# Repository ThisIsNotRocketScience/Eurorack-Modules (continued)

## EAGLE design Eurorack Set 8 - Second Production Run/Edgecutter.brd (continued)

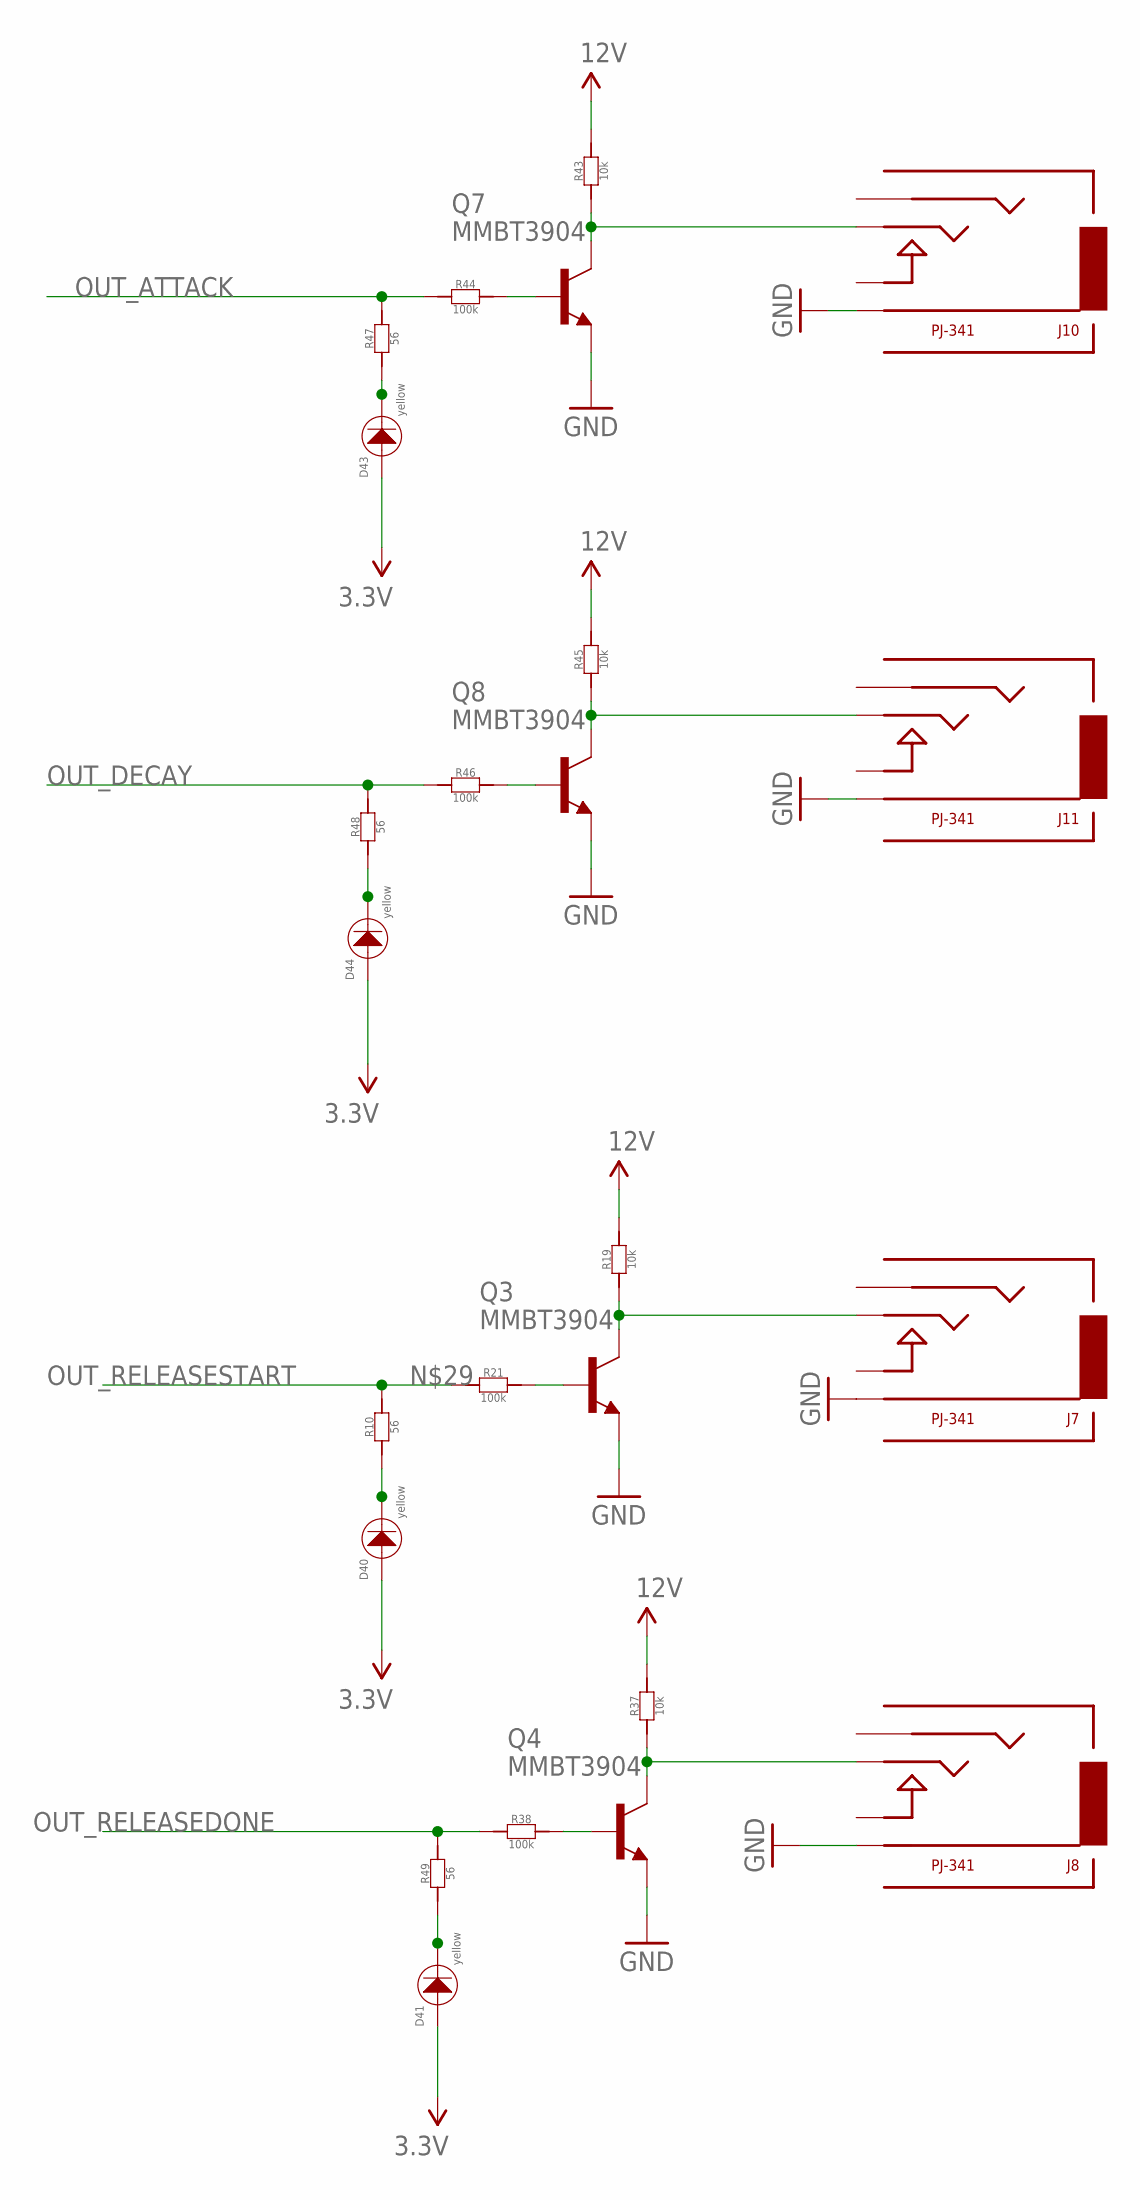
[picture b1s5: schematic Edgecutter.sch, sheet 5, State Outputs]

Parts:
D40, D41, D43, D44: yellow; 3MMLED
J7, J8, J10, J11: PJ-341; 3.5MM-JACK-SWITCH-13MM-OUTPUT
Q3, Q4, Q7, Q8: MMBT3904; SOT23-BEC; MPN PMBT3904,215
R10, R47, R48, R49: 56; R0603
R19, R37, R43, R45: 10k; R0603
R21, R38, R44, R46: 100k; R0603

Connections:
3.3V: D40.+, D41.+, D43.+, D44.+; also elsewhere on the board
12V: R19.2, R37.2, R43.2, R45.2; also elsewhere on the board
D21: D43.-, R47.1
GND: J7.RING@3 (RING), J8.RING@3 (RING), J10.RING@3 (RING), J11.RING@3 (RING), Q3.E, Q4.E, Q7.E, Q8.E; also elsewhere on the board
unnamed: D40.-, R10.1
unnamed: Q3.B, R21.2
unnamed: J7.TIP@3 (TIP), Q3.C, R19.1
unnamed: D41.-, R49.1
unnamed: D44.-, R48.1
unnamed: Q4.B, R38.2
unnamed: J8.TIP@3 (TIP), Q4.C, R37.1
unnamed: Q7.B, R44.2
unnamed: J10.TIP@3 (TIP), Q7.C, R43.1
unnamed: Q8.B, R46.2
unnamed: J11.TIP@3 (TIP), Q8.C, R45.1
OUT_ATTACK: R44.1, R47.2; also elsewhere on the board
OUT_DECAY: R46.1, R48.2; also elsewhere on the board
OUT_RELEASEDONE: R38.1, R49.2; also elsewhere on the board
OUT_RELEASESTART: R10.2, R21.1; also elsewhere on the board

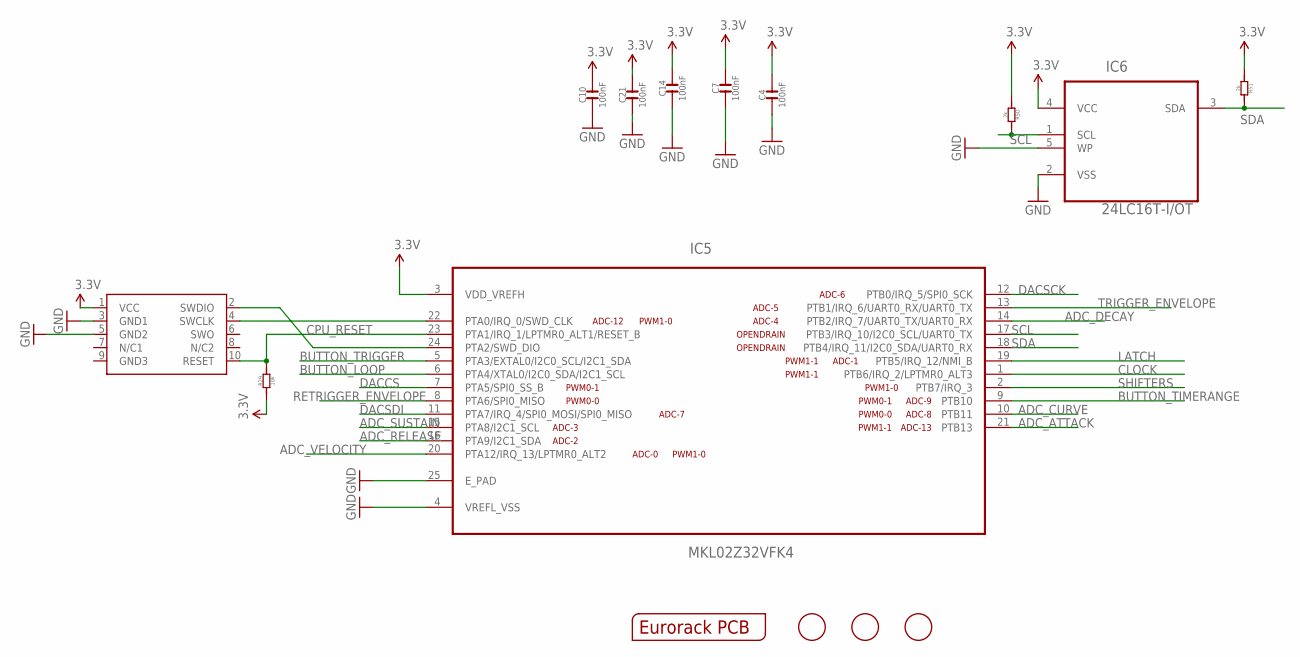
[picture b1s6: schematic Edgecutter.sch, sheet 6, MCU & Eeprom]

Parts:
C4, C7, C10, C14, C21: 100nF; C0603; MPN MC0603F104Z160CT
FID1, FID2, FID3: FIDUCIAL; FIDUCIAL_1MM
IC5: MKL02Z32VFK4; QFN50P400X400X100-25N
IC6: 24LC16T-I/OT; SOT95P290X145-5N; MPN 24LC16T-I/OT
OUTLINE: EURORACK_PCB12HP; EURORACK12HPPCB
R29: 10k; R0603
R50, R51: 2k; R0603
SWD1: CORTEX_SWD; M50-3600542

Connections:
3.3V: C4.2, C7.2, C10.2, C14.2, C21.2, IC5.3 (VDD_VREFH), IC6.4 (VCC), R29.1, R50.1, R51.1, SWD1.1 (VCC); also elsewhere on the board
ADC_ATTACK: IC5.21 (PTB13); also elsewhere on the board
ADC_CURVE: IC5.10 (PTB11); also elsewhere on the board
ADC_DECAY: IC5.14 (PTB2/IRQ_7/UART0_TX/UART0_RX); also elsewhere on the board
ADC_RELEASE: IC5.16 (PTA9/I2C1_SDA); also elsewhere on the board
ADC_SUSTAIN: IC5.15 (PTA8/I2C1_SCL); also elsewhere on the board
ADC_VELOCITY: IC5.20 (PTA12/IRQ_13/LPTMR0_ALT2); also elsewhere on the board
BUTTON_LOOP: IC5.6 (PTA4/XTAL0/I2C0_SDA/I2C1_SCL); also elsewhere on the board
BUTTON_TIMERANGE: IC5.9 (PTB10); also elsewhere on the board
BUTTON_TRIGGER: IC5.5 (PTA3/EXTAL0/I2C0_SCL/I2C1_SDA); also elsewhere on the board
CLOCK: IC5.1 (PTB6/IRQ_2/LPTMR0_ALT3); also elsewhere on the board
CPU_RESET: IC5.23 (PTA1/IRQ_1/LPTMR0_ALT1/RESET_B), R29.2, SWD1.10 (RESET)
DACCS: IC5.7 (PTA5/SPI0_SS_B); also elsewhere on the board
DACSCK: IC5.12 (PTB0/IRQ_5/SPI0_SCK); also elsewhere on the board
DACSDI: IC5.11 (PTA7/IRQ_4/SPI0_MOSI/SPI0_MISO); also elsewhere on the board
GND: C4.1, C7.1, C10.1, C14.1, C21.1, IC5.4 (VREFL_VSS), IC5.25 (E_PAD), IC6.2 (VSS), IC6.5 (WP), SWD1.3 (GND1), SWD1.5 (GND2); also elsewhere on the board
LATCH: IC5.19 (PTB5/IRQ_12/NMI_B); also elsewhere on the board
RETRIGGER_ENVELOPE: IC5.8 (PTA6/SPI0_MISO); also elsewhere on the board
SCL: IC5.17 (PTB3/IRQ_10/I2C0_SCL/UART0_TX), IC6.1 (SCL), R50.2
SDA: IC5.18 (PTB4/IRQ_11/I2C0_SDA/UART0_RX), IC6.3 (SDA), R51.2
SHIFTERS: IC5.2 (PTB7/IRQ_3); also elsewhere on the board
SWD_CLK: IC5.22 (PTA0/IRQ_0/SWD_CLK), SWD1.4 (SWCLK)
SWD_DIO: IC5.24 (PTA2/SWD_DIO), SWD1.2 (SWDIO)
TRIGGER_ENVELOPE: IC5.13 (PTB1/IRQ_6/UART0_RX/UART0_TX); also elsewhere on the board

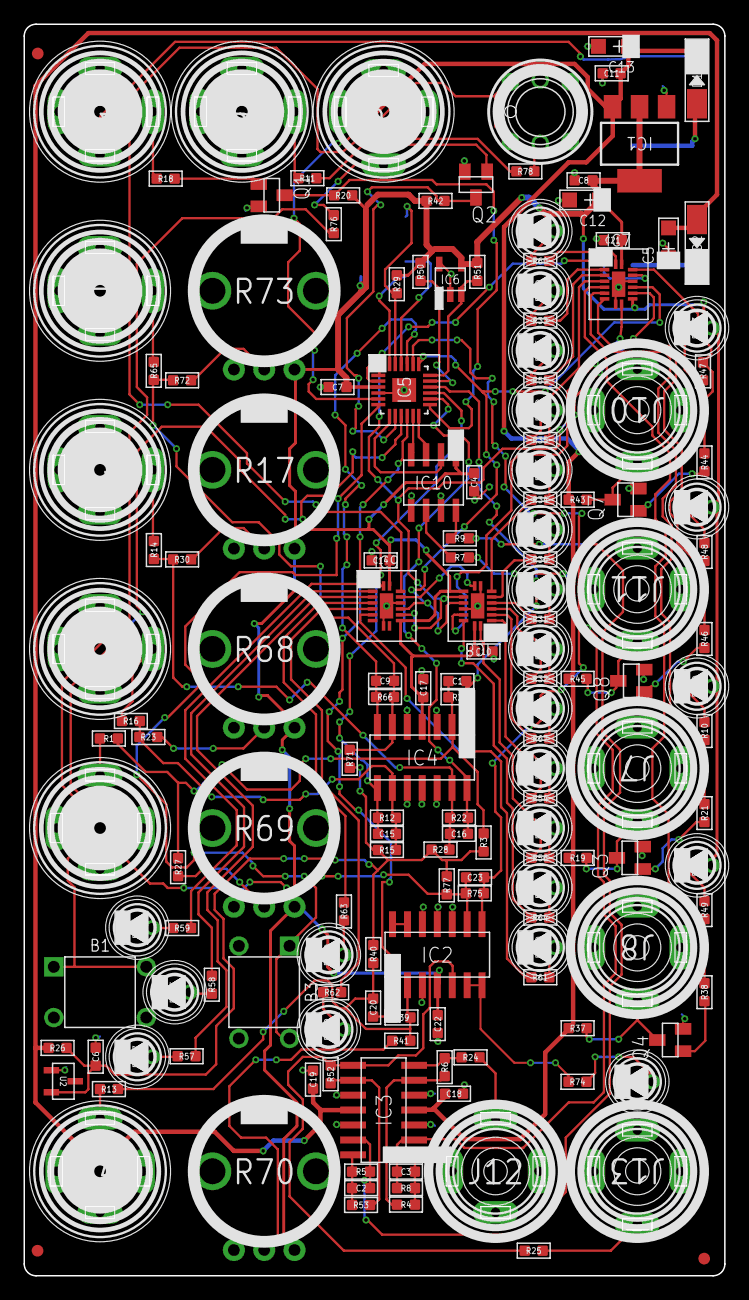
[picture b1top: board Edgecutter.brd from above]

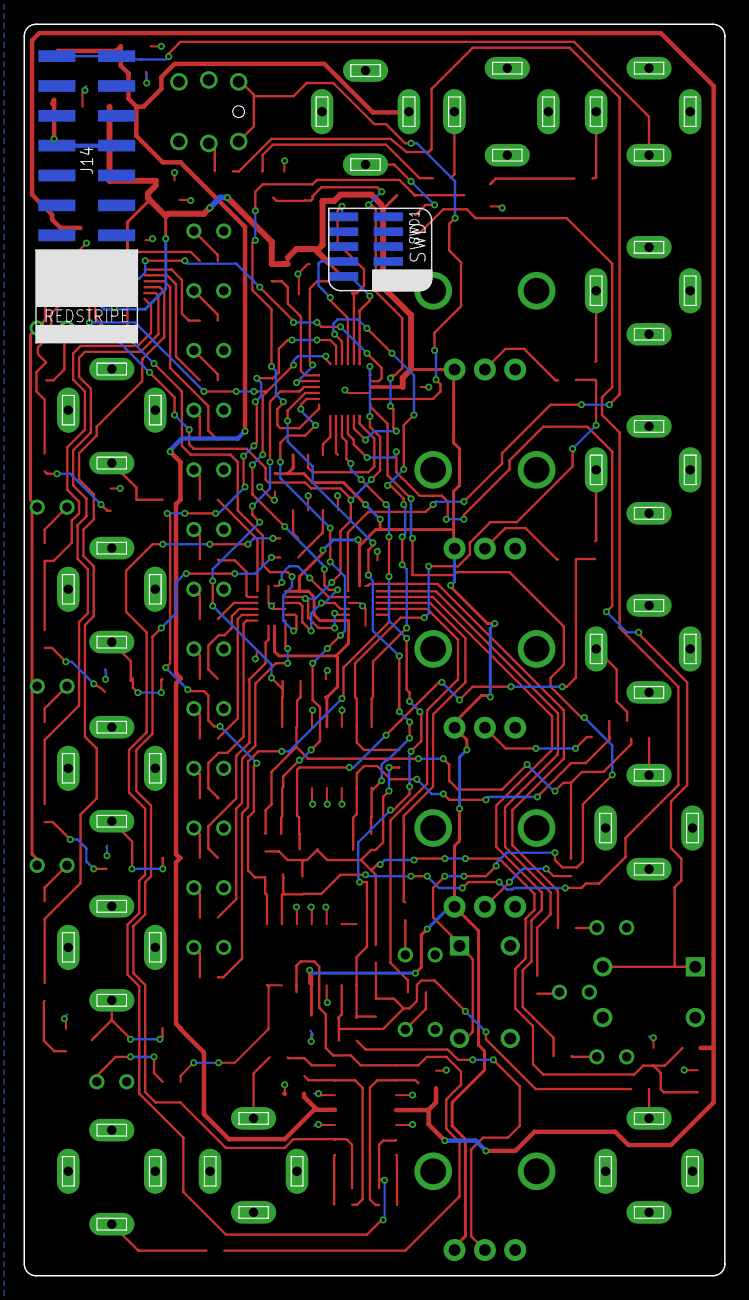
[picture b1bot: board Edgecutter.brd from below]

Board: 2 copper layers, 59.6 x 106.5 mm, 166 parts (2 on the bottom side), 122 nets.

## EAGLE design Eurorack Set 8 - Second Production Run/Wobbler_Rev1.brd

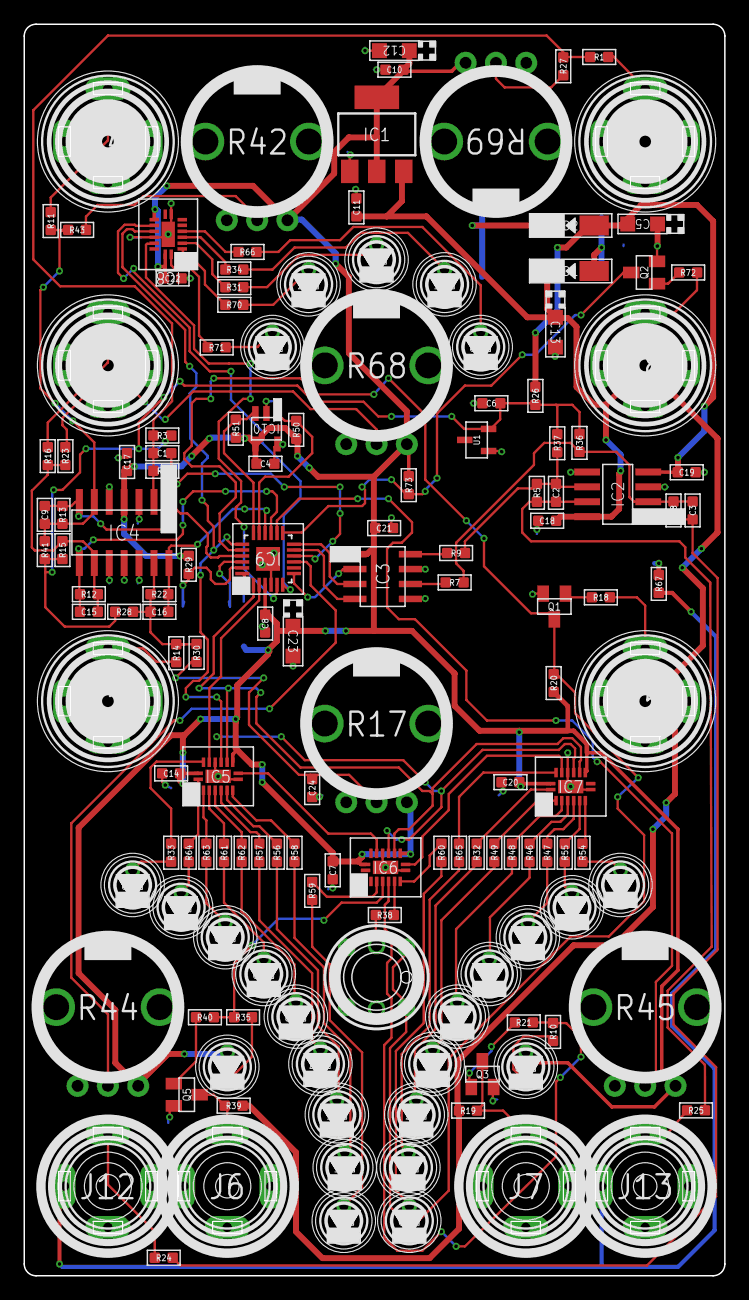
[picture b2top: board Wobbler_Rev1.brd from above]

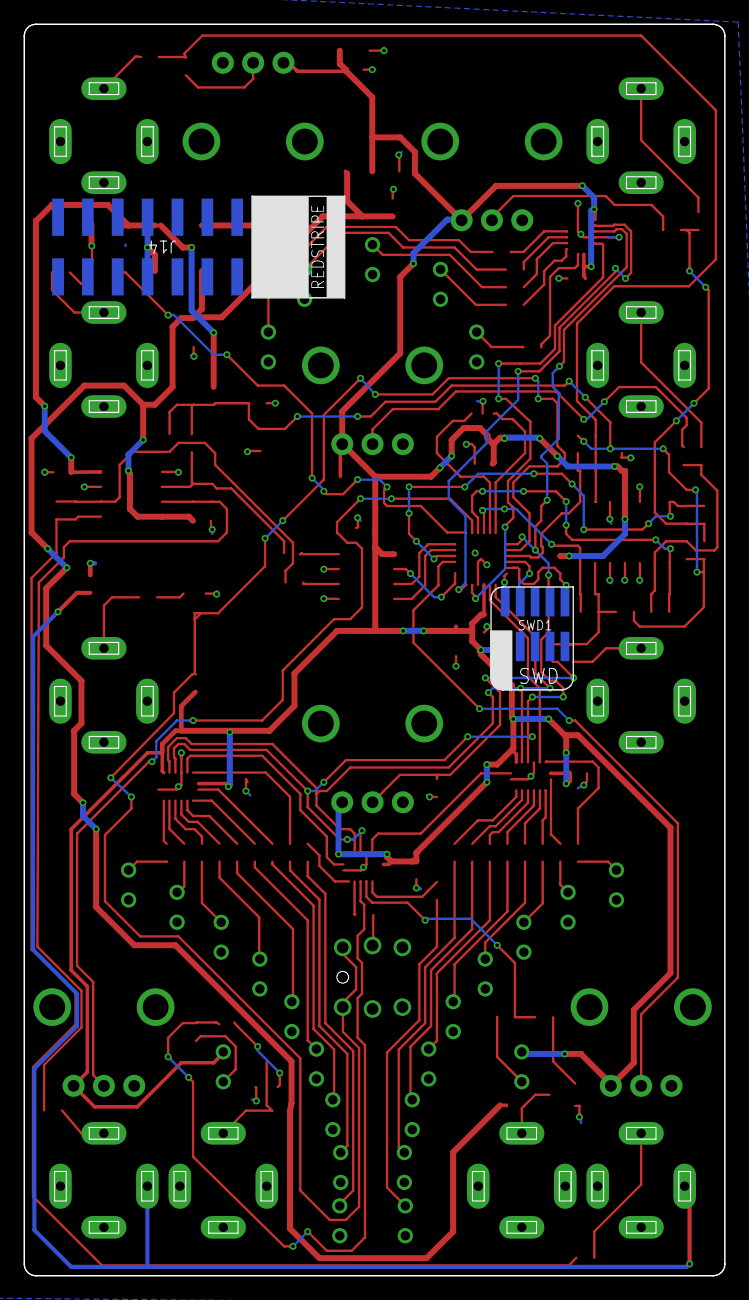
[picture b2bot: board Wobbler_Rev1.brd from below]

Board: 2 copper layers, 59.6 x 106.5 mm, 149 parts (2 on the bottom side), 111 nets.

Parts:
C1, C9, C15, C16: 3.3nF; C0603
C2: 3.3nF C0G; C0603
C3: 3.3nF COG; C0603
C4, C6, C7, C8, C10, C11, C14, C17, C18, C19, C20, C21, C22, C24: 100nF; C0603
C5, C12, C13, C23: 10uF; AVX-A
D1, D2: MRA4004T3G; DO-214AC
D3, D4, D5, D6, D7, D8, D9, D10, D11, D12, D13, D14, D24, D25, D26, D27, D28, D29, D30, D31, D32, D33, D34, D35, D40: yellow; 3MMLED
IC1: LD1117AS33TR; SOT223
IC2: TL072; SO08
IC3: MCP4822-E/SN; SOIC8-N_MC
IC4: MCP6004; SO14
IC5, IC6, IC7, IC8: 74HC595BQ; QFN50P250X350X100-17N
IC9: MKL02Z32VFK4; QFN50P400X400X100-25N
IC10: 24LC16T-I/OT; SOT95P290X145-5N
J1, J2, J3, J4, J5, J8: PJ-341; 3.5MM-JACK-SWITCH-13MM-INPUT
J6, J7, J12, J13: PJ-341; 3.5MM-JACK-SWITCH-13MM-OUTPUT
J14: POWERSMT; 2X08_SMT_HEADER
OUTLINE: EURORACK_PCB12HP; EURORACK12HPPCB
Q1, Q2, Q3, Q5: MMBT3904; SOT23-BEC
R1, R11, R14, R16, R18, R21, R40, R72: 100k; R0603
R2, R12, R13, R22, R23, R27, R30, R43: 33k; R0603
R3, R15, R28, R41: 51k; R0603
R5, R8, R36, R37: 187k 0.1%; R0603
R7, R9: 38.3k 0.1%; R0603
R10, R31, R32, R33, R34, R35, R38, R46, R47, R48, R49, R54, R55, R56, R57, R58, R59, R60, R61, R62, R63, R64, R65, R66, R70, R71: 56; R0603
R17, R42, R44, R45, R68, R69: 10kB; OG-POTS_ALPS_POT_VERTICAL
R19, R20, R26, R29, R39, R73: 10k; R0603
R24, R25: 100; R0603
R50, R51: 2k; R0603
R67: 0; R0603
SWD1: CORTEX_SWD; M50-3600542
U1: LM4040DIM3-5.0; SOT95P237X112-3N
U$1: SWITCH_W_LED_PB6149L-X-102YELLOW; PB6149L

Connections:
3.3V: C4.2, C7.2, C8.2, C10.2, C12.+, C14.2, C17.1, C20.2, C21.2, C22.2, C23.+, D3.+, D40.+, IC1.2, IC1.4, IC3.1, IC4.4, IC5.10, IC5.16, IC6.10, IC6.16, IC7.10, IC7.16, IC8.10, IC8.16, IC9.3, IC10.4, R17.P$3, R20.2, R29.1, R42.P$3, R44.P$3, R45.P$3, R50.1, R51.1, R68.P$3, R69.P$3, R73.2, SWD1.1
12V: C11.2, C13.+, C18.2, D1.2, IC1.3, IC2.8, R19.2, R39.2
-12V: C5.-, C19.2, D2.1, IC2.4, R26.1
ADC_FREQ: C16.2, IC4.14, IC9.16, R22.1
ADC_MOD: C1.2, IC4.1, IC9.21, R2.1
ADC_NORMAL: IC9.9, R44.P$2
ADC_PHASE: C9.2, IC4.7, IC9.10, R13.1
ADC_PHASED: IC9.14, R45.P$2
ADC_SHAPE: C15.2, IC4.8, IC9.15, R12.1
CLOCK: IC5.11, IC6.11, IC7.11, IC9.1
CLOCK_2: IC8.11, IC9.6
CPU_RESET: IC9.23, R29.2, SWD1.10
DACCS: IC3.2, IC9.7
DACSCK: IC3.3, IC9.12
DACSDI: IC3.4, IC9.11
GND: C4.1, C5.+, C6.1, C7.1, C8.1, C10.1, C11.1, C12.-, C13.-, C14.1, C17.2, C18.1, C19.1, C20.1, C21.1, C22.1, C23.-, C24.2, D4.-, D5.-, D6.-, D7.-, D8.-, D9.-, D10.-, D11.-, D12.-, D13.-, D14.-, D24.-, D25.-, D26.-, D27.-, D28.-, D29.-, D30.-, D31.-, D32.-, D33.-, D34.-, D35.-, IC1.1, IC2.3, IC2.5, IC3.5, IC3.7, IC4.3, IC4.5, IC4.10, IC4.11, IC4.12, IC5.8, IC5.13, IC5.17, IC6.8, IC6.13, IC6.17, IC7.8, IC7.13, IC7.17, IC8.8, IC8.13, IC8.17, IC9.4, IC9.25, IC10.2, IC10.5, J1.RING@3, J1.SWITCH@3, J2.RING@3, J2.SWITCH@3, J3.RING@3, J3.SWITCH@3, J4.RING@3, J4.SWITCH@3, J5.RING@3, J5.SWITCH@3, J6.RING@3, J7.RING@3, J8.RING@3, J8.SWITCH@3, J14.3, J14.4, J14.5, J14.6, J14.7, J14.8, Q1.E, Q2.E, Q3.E, Q5.E, R17.P$1, R42.P$1, R44.P$1, R45.P$1, R67.1, R68.P$1, R69.P$1, SWD1.3, SWD1.5, U1.1, U$1.3, U$1.4, U$1.LEDNEG
KNOB_FREQ: C24.1, R17.P$2, R30.2
KNOB_MOD: R27.2, R69.P$2
KNOB_PHASE: R42.P$2, R43.2
KNOB_SHAPE: R23.2, R68.P$2
LATCH: IC5.12, IC6.12, IC7.12, IC8.12, IC9.19
unnamed: IC5.15, R33.2
unnamed: J2.TIP@3, R16.2
unnamed: C15.1, IC4.9, R12.2, R15.1, R16.1, R23.1
unnamed: IC3.8, R9.2
unnamed: J3.TIP@3, R1.2
unnamed: IC3.6, R7.2
unnamed: C1.1, IC4.2, R1.1, R2.2, R3.1, R27.1
unnamed: C2.1, IC2.6, R5.2, R9.1, R37.1
unnamed: C3.1, IC2.2, R7.1, R8.2, R36.1
unnamed: J4.TIP@3, R11.2
unnamed: C9.1, IC4.6, R11.1, R13.2, R41.1, R43.1
unnamed: D1.1, J14.9, J14.10
unnamed: D7.+, R47.1
unnamed: Q1.B, R18.2
unnamed: J5.TIP@3, R18.1
unnamed: IC5.1, R64.2
unnamed: J13.TIP@3, R25.1
unnamed: J12.TIP@3, R24.1
unnamed: IC5.2, R63.2
unnamed: D40.-, R10.1
unnamed: Q3.B, R21.2
unnamed: IC5.3, R61.2
unnamed: D3.-, R35.1
unnamed: D28.+, R62.1
unnamed: J7.TIP@3, Q3.C, R19.1
unnamed: IC5.4, R62.2
unnamed: IC5.5, R57.2
unnamed: D29.+, R61.1
unnamed: J1.TIP@3, R14.2
unnamed: C16.1, IC4.13, R14.1, R22.2, R28.1, R30.1
unnamed: IC5.6, R56.2
unnamed: IC5.7, R58.2
unnamed: IC6.3, R59.2
unnamed: IC7.7, R54.2
unnamed: IC7.6, R55.2
unnamed: IC7.5, R47.2
unnamed: R38.1, U$1.LEDPOS
unnamed: D13.+, R70.1
unnamed: IC7.4, R46.2
unnamed: Q2.B, R72.2
unnamed: J8.TIP@3, R72.1
unnamed: D6.+, R46.1
unnamed: D5.+, R48.1
unnamed: D4.+, R49.1
unnamed: D8.+, R55.1
unnamed: D9.+, R54.1
unnamed: D10.+, R60.1
unnamed: D11.+, R65.1
unnamed: IC7.3, R48.2
unnamed: IC7.2, R49.2
unnamed: IC7.1, R32.2
unnamed: IC7.15, R65.2
unnamed: IC6.7, R60.2
unnamed: D14.+, R71.1
unnamed: IC8.1, R71.2
unnamed: Q5.B, R40.2
unnamed: J6.TIP@3, Q5.C, R39.1
unnamed: IC8.2, R70.2
unnamed: D2.2, J14.1, J14.2
unnamed: D12.+, R66.1
unnamed: IC8.3, R31.2
unnamed: IC8.4, R34.2
unnamed: IC8.5, R66.2
unnamed: D27.+, R57.1
unnamed: D26.+, R56.1
unnamed: D25.+, R58.1
unnamed: D24.+, R59.1
unnamed: D30.+, R63.1
unnamed: D31.+, R64.1
unnamed: D32.+, R33.1
unnamed: D33.+, R32.1
unnamed: D34.+, R31.1
unnamed: D35.+, R34.1
NORMALOUT: C3.2, IC2.1, R8.1, R24.2
OUT_LFOCYCLEMID: IC6.5, R10.2, R21.1
OUT_LFOCYCLESTART: IC6.4, R35.2, R40.1
PHASEDOUT: C2.2, IC2.7, R5.1, R25.2
REF_-5V: C6.2, R3.2, R15.2, R26.2, R28.2, R36.2, R37.2, R41.2, U1.2
RESET_PATTERN: IC9.20, Q1.C, R20.1, U$1.1, U$1.2
RETURNGROUND: J12.RING@3, J13.RING@3, R67.2
SCL: IC9.17, IC10.1, R50.2
SDA: IC9.18, IC10.3, R51.2
SHIFTER1TO2: IC5.9, IC6.14
SHIFTERS: IC5.14, IC9.2
SHIFTERS2TO3: IC6.9, IC7.14
SHIFTERS_2: IC8.14, IC9.5
SWD_CLK: IC9.22, SWD1.4
SWD_DIO: IC9.24, SWD1.2
SYNC_LFO: IC9.13, Q2.C, R73.1
TRIGGERBUTTONLED: IC6.6, R38.2

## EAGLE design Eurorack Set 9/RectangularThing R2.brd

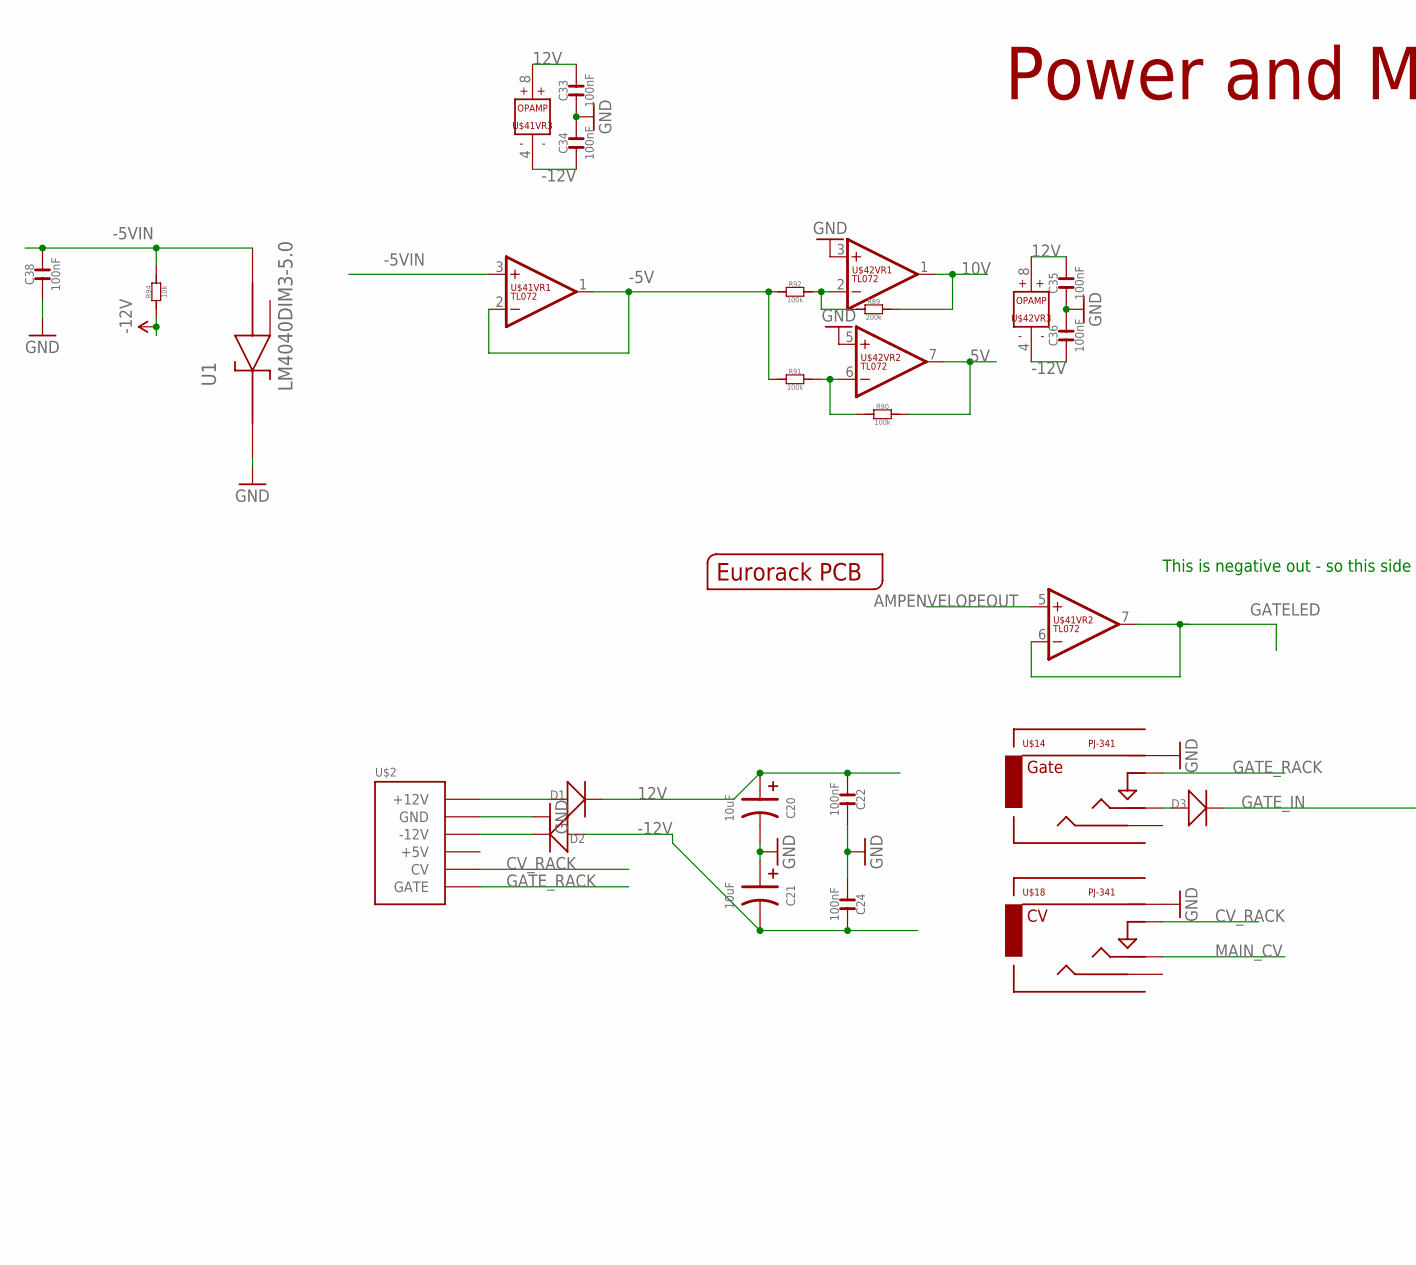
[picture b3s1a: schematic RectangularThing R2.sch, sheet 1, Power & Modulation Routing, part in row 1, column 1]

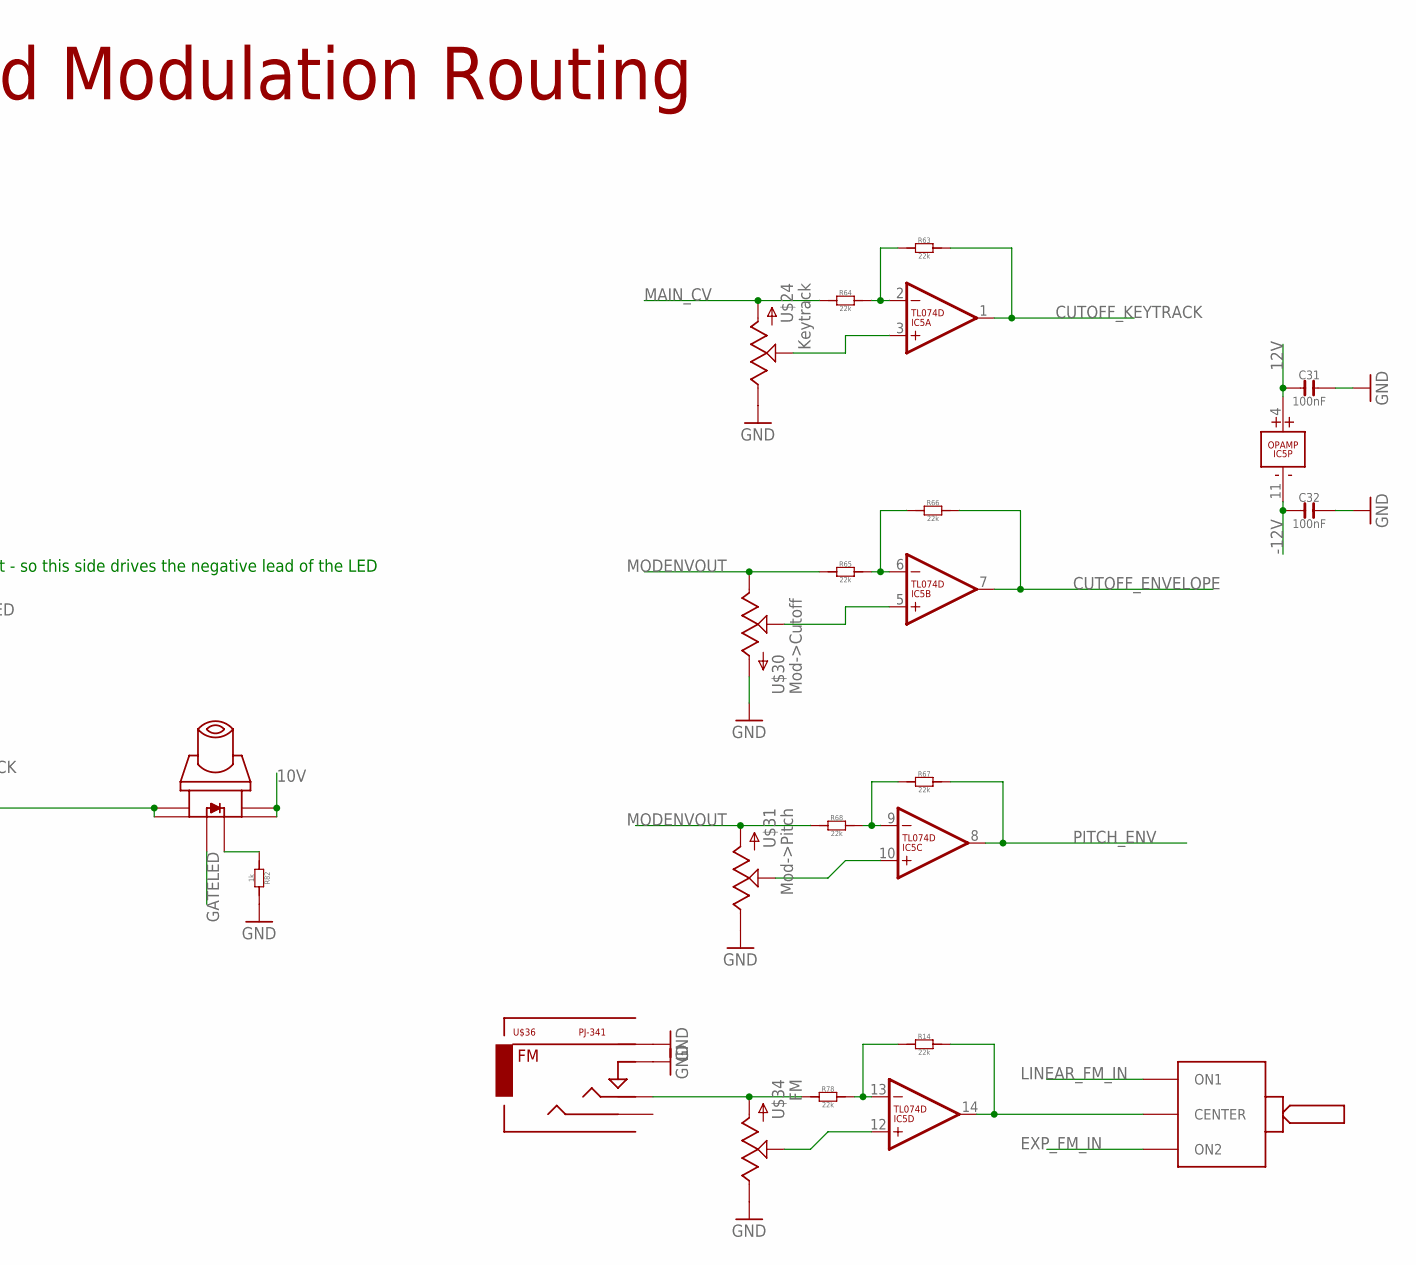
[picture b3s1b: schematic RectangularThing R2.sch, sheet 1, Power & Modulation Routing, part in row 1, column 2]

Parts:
C20, C21: 10uF; AVX-A
C22, C24, C31, C32, C33, C34, C35, C36: 100nF; C0603
C38: 100nF; C0603; MPN 06035C104KAT2A
D1, D2, D3: D-SMA; DO-214AC
IC5: TL074D; SO14
R14, R63, R64, R65, R66, R67, R68, R78: 22k; R0603
R82: 1k; R0603
R89: 200k; R0603
R90, R91, R92: 100k; R0603
R94: 10k; R0603
U1: LM4040DIM3-5.0; SOT95P237X112-3N
U$1: EURORACK_PCB20HP_10X10CM; EURORACK20HP_10X10CM
U$2: POWERSHROUDED; POWER_16_SHROUDED
U$14, U$18, U$36: PJ-341; 3.5MM-JACK-SWITCH-13MM-INPUT
U$24, U$30, U$31, U$34: POTZEPHPOT; OG-POTS_ALPS_POT_VERTICAL
U$35: ONOFFON; MULTICOMP1MS-ONOFFON
U$39: SWITCH_W_LED_PB6149L-X-102YELLOW; PB6149L
U$41, U$42: TL072; SO08

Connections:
5V: R90.2, U$42.7 (OUT); also elsewhere on the board
10V: R89.2, U$39.3, U$39.4, U$42.1 (OUT); also elsewhere on the board
12V: C20.+ (1), C22.1, C31.1, C33.2, C35.2, D1.2 (-), IC5.4 (V+), U$41.8 (V+), U$42.8 (V+); also elsewhere on the board
-5V: R91.1, R92.1, U$41.1 (OUT), U$41.2 (-IN); also elsewhere on the board
-5VIN: C38.2, R94.2, U1.2 (ANODE), U$41.3 (+IN)
-12V: C21.- (2), C24.2, C32.1, C34.1, C36.1, D2.1 (+), IC5.11 (V-), R94.1, U$41.4 (V-), U$42.4 (V-); also elsewhere on the board
AMPENVELOPEOUT: U$41.5 (+IN); also elsewhere on the board
CUTOFF_ENVELOPE: IC5.7 (OUT), R66.2; also elsewhere on the board
CUTOFF_KEYTRACK: IC5.1 (OUT), R63.2; also elsewhere on the board
CV_RACK: U$2.13 (CV), U$2.14 (CV), U$18.SWITCH@3 (SWITCH)
EXP_FM_IN: U$35.3 (ON2); also elsewhere on the board
GATELED: U$39.LEDPOS (POS), U$41.6 (-IN), U$41.7 (OUT)
GATE_IN: D3.2 (-), U$39.1, U$39.2; also elsewhere on the board
GATE_RACK: U$2.15 (GATE), U$2.16 (GATE), U$14.SWITCH@3 (SWITCH)
GND: C20.- (2), C21.+ (1), C22.2, C24.1, C31.2, C32.2, C33.1, C34.2, C35.1, C36.2, C38.1, R82.2, U1.1 (CATHODE), U$2.3 (GND), U$2.4 (GND), U$2.5 (GND), U$2.6 (GND), U$2.7 (GND), U$2.8 (GND), U$14.RING@3 (RING), U$18.RING@3 (RING), U$24.P$1 (E), U$30.P$3 (A), U$31.P$1 (E), U$34.P$1 (E), U$36.RING@3 (RING), U$36.SWITCH@3 (SWITCH), U$42.3 (+IN), U$42.5 (+IN); also elsewhere on the board
LINEAR_FM_IN: U$35.1 (ON1); also elsewhere on the board
MAIN_CV: R64.1, U$18.TIP@3 (TIP), U$24.P$3 (A); also elsewhere on the board
MODENVOUT: R65.1, R68.1, U$30.P$1 (E), U$31.P$3 (A); also elsewhere on the board
unnamed: D1.1 (+), U$2.9 (+12V), U$2.10 (+12V)
unnamed: D2.2 (-), U$2.1 (-12V), U$2.2 (-12V)
unnamed: R82.1, U$39.LEDNEG (NEG)
unnamed: IC5.14 (OUT), R14.2, U$35.2 (CENTER)
unnamed: IC5.13 (-IN), R14.1, R78.2
unnamed: IC5.2 (-IN), R63.1, R64.2
unnamed: IC5.3 (+IN), U$24.P$2 (S)
unnamed: IC5.6 (-IN), R65.2, R66.1
unnamed: IC5.9 (-IN), R67.1, R68.2
unnamed: IC5.5 (+IN), U$30.P$2 (S)
unnamed: IC5.10 (+IN), U$31.P$2 (S)
unnamed: IC5.12 (+IN), U$34.P$2 (S)
unnamed: R78.1, U$34.P$3 (A), U$36.TIP@3 (TIP)
unnamed: D3.1 (+), U$14.TIP@3 (TIP)
unnamed: R89.1, R92.2, U$42.2 (-IN)
unnamed: R90.1, R91.2, U$42.6 (-IN)
PITCH_ENV: IC5.8 (OUT), R67.2; also elsewhere on the board

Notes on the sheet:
This is negative out - so this side drives the negative lead of the LED
Power and Modulation Routing

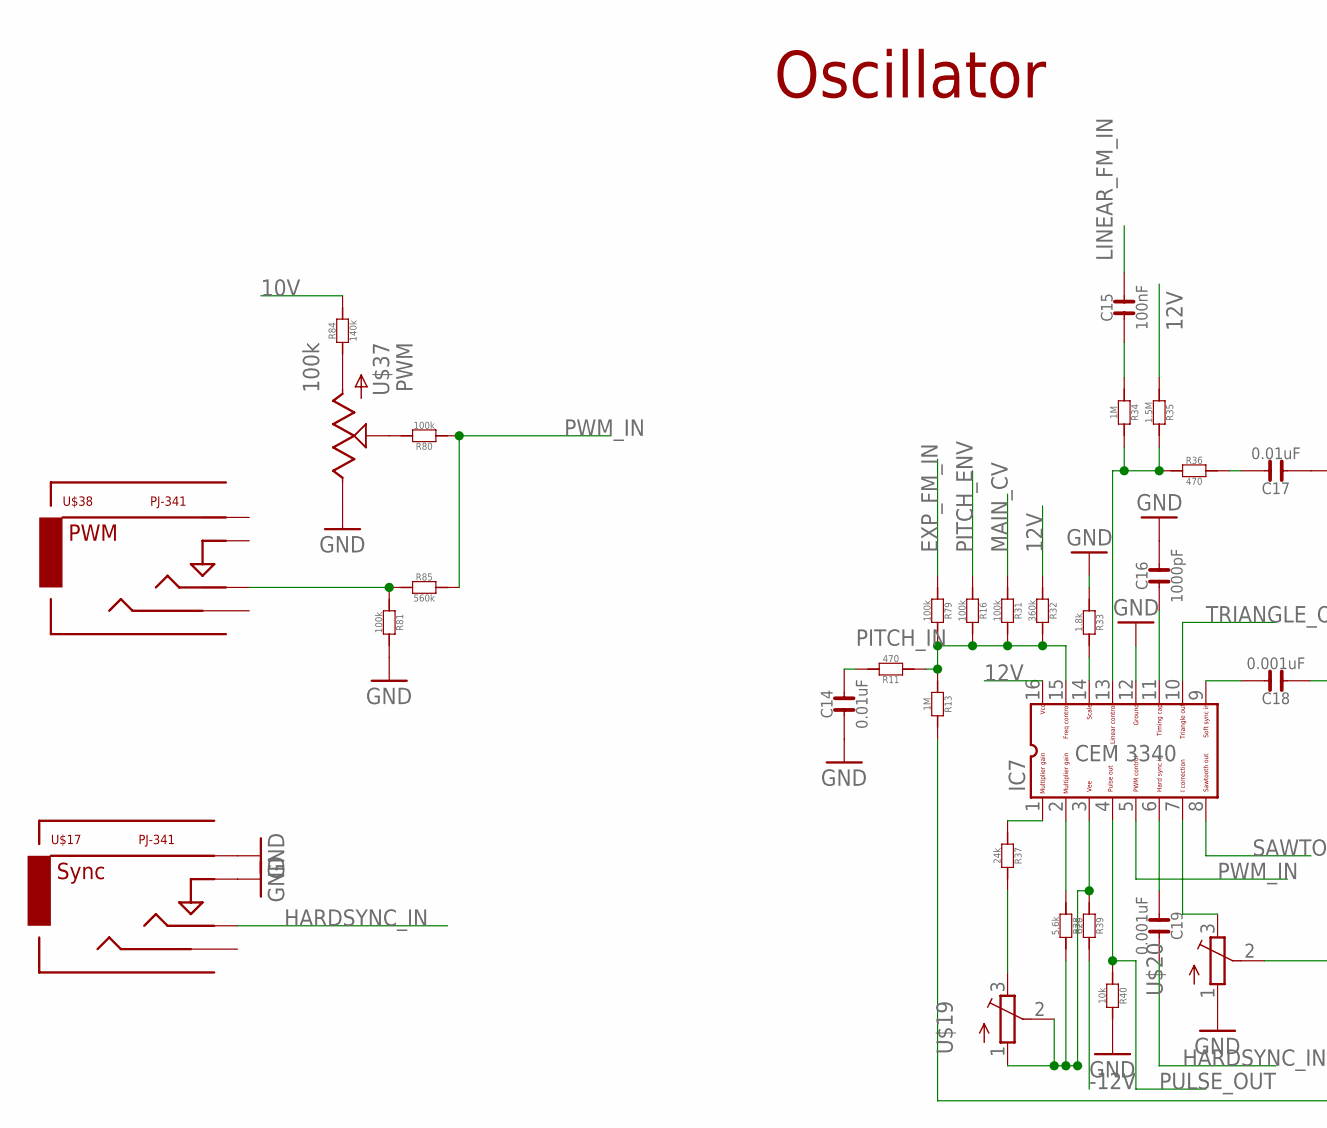
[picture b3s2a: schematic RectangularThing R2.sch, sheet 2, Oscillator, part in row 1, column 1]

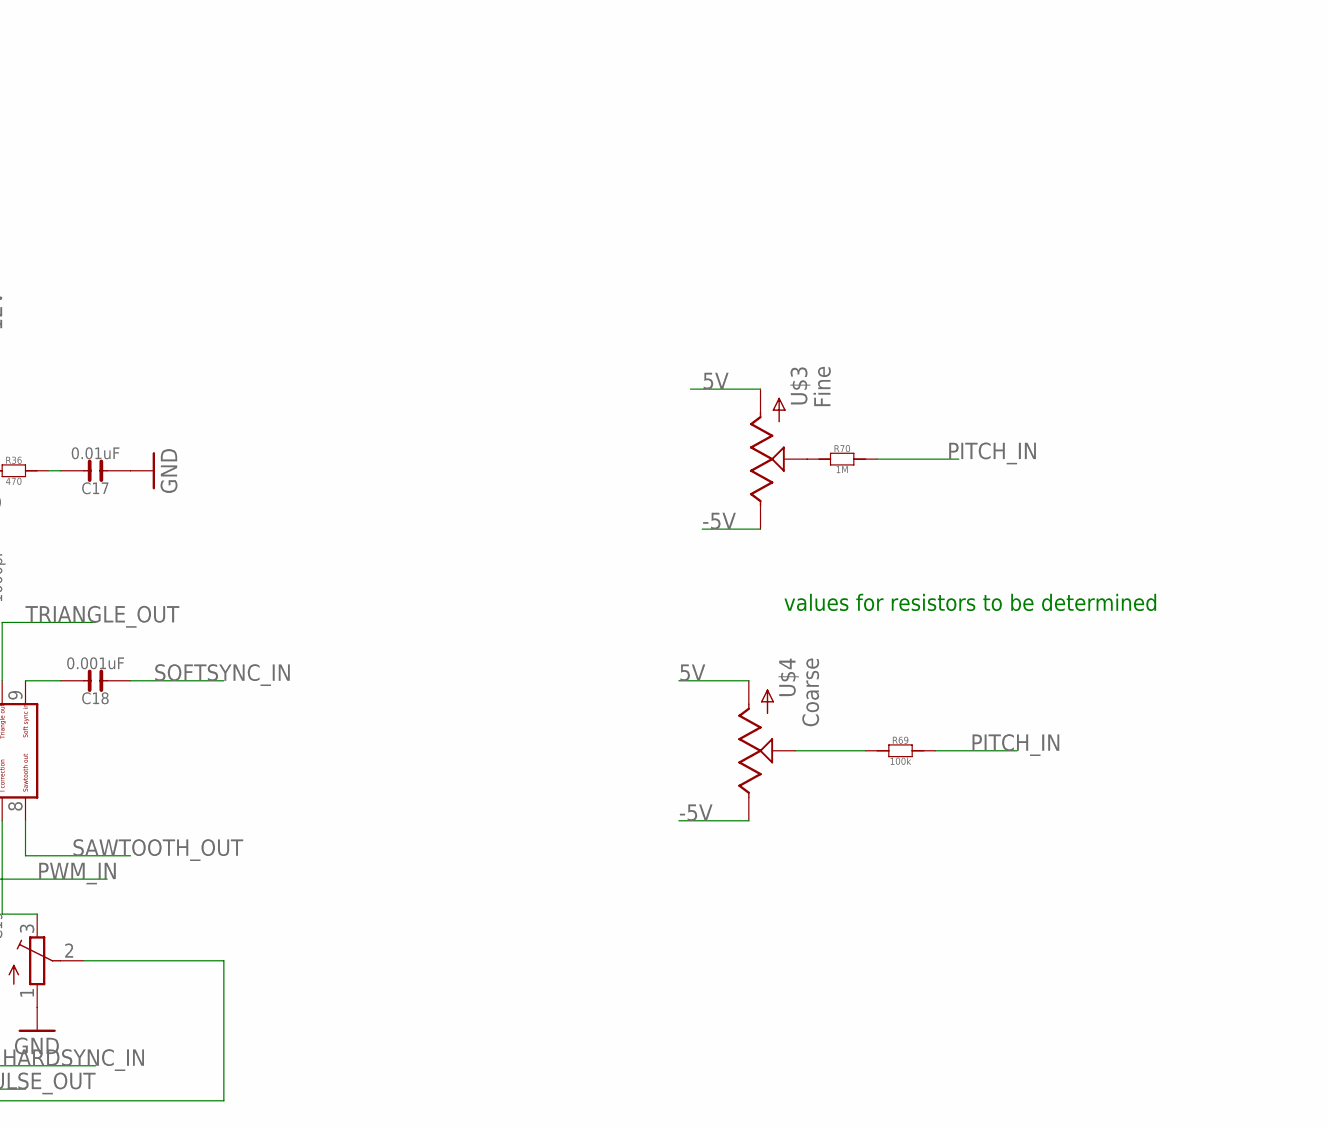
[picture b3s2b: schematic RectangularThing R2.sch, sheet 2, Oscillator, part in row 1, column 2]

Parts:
C14, C17: 0.01uF; C0603
C15: 100nF; C0603
C16: 1000pF; C0603
C18, C19: 0.001uF; C0603
IC7: CEM3340; DIL16
R11, R36: 470; R0603
R13, R34, R70: 1M; R0603
R16, R31, R69, R79, R80, R81: 100k; R0603
R32: 360k; R0603
R33: 1.8k; R0603
R35: 1.5M; R0603
R37: 24k; R0603
R38: 5.6k; R0603
R39: 820; R0603
R40: 10k; R0603
R84: 140k; R0603
R85: 560k; R0603
U$3, U$4: POTZEPHPOT; OG-POTS_ALPS_POT_VERTICAL
U$17, U$38: PJ-341; 3.5MM-JACK-SWITCH-13MM-INPUT
U$19, U$20: TRIMPOTTC33X; TC33X
U$37: 100k; OG-POTS_ALPS_POT_VERTICAL

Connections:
5V: U$3.P$3 (A), U$4.P$3 (A); also elsewhere on the board
10V: R84.2; also elsewhere on the board
12V: IC7.16, R32.1, R35.1; also elsewhere on the board
-5V: U$3.P$1 (E), U$4.P$1 (E); also elsewhere on the board
-12V: R39.2; also elsewhere on the board
EXP_FM_IN: R79.1; also elsewhere on the board
GND: C14.1, C16.2, C17.1, IC7.12, R33.1, R40.2, R81.2, U$17.RING@3 (RING), U$17.SWITCH@3 (SWITCH), U$20.1 (A), U$37.P$1 (E); also elsewhere on the board
HARDSYNC_IN: C19.2, U$17.TIP@3 (TIP)
LINEAR_FM_IN: C15.2; also elsewhere on the board
MAIN_CV: R31.1; also elsewhere on the board
unnamed: C14.2, R11.2
unnamed: C17.2, R36.2
unnamed: IC7.13, R34.2, R35.2, R36.1
unnamed: C15.1, R34.1
unnamed: C16.1, IC7.11
unnamed: C18.2, IC7.9
unnamed: IC7.14, R33.2
unnamed: C19.1, IC7.6
unnamed: IC7.1, R37.1
unnamed: R37.2, U$19.3 (E)
unnamed: IC7.3, R38.2, R39.1, U$19.1 (A), U$19.2 (S)
unnamed: R13.2, U$20.2 (S)
unnamed: IC7.2, R38.1
unnamed: IC7.7, U$20.3 (E)
unnamed: R69.1, U$4.P$2 (S)
unnamed: R70.1, U$3.P$2 (S)
unnamed: R80.2, U$37.P$2 (S)
unnamed: R84.1, U$37.P$3 (A)
unnamed: R81.1, R85.1, U$38.TIP@3 (TIP)
PITCH_ENV: R16.1; also elsewhere on the board
PITCH_IN: IC7.15, R11.1, R13.1, R16.2, R31.2, R32.2, R69.2, R70.2, R79.2
PULSE_OUT: IC7.4, R40.1; also elsewhere on the board
PWM_IN: IC7.5, R80.1, R85.2
SAWTOOTH_OUT: IC7.8; also elsewhere on the board
SOFTSYNC_IN: C18.1
TRIANGLE_OUT: IC7.10; also elsewhere on the board

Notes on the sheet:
Oscillator
values for resistors to be determined

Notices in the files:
parts and their libraries:
SparkFun-Aesthetics: Licensing: CC v3.0 Share-Alike You are welcome to use this library for commercial purposes.
